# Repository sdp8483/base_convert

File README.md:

# Base Convert Rev A 
## Introduction
Base Convert PL-47710 Rev. A is a simple desk/handheld device to convert between hexadecimal, decimal, and binary. The unit features separate displays for each number base for easy comparison between the three bases. User input is possible using 16 alphanumeric keys and an input mode selector switch. The device is powered by 4 AA alkaline batteries with an estimated 100 hours of battery life.

## Specifications
|Item             |Specification               |
|:----------------|:--------------------------:|
|Hex Display      |4 digit, 7 segment red LED  |
|Decimal Display  |6 digit, 7 segment red LED  |
|Binary Display   |16 red LEDs                 |
|User Input       |16 digit alphanumeric keypad|
|Power            |4 AA Alkaline               |
|Battery Life     |100 hrs estimated           |
|Width            |94mm / 3.7"                 |
|Height           |100mm / 3.94"               |
|Thickness        |35mm / 1.38"                |
|Weight, with 4xAA|275g / 9.65oz               |

## Layout

1. Hexadecimal Display
2. Decimal Display
3. Binary Display
4. Power and Input Selection Switch
5. Alphanumeric Input Keypad
6. Programming Port (Right Angle Header on Side)

## Installing Batteries
Using a 1.5mm hex bit remove the eight M2.5 button head hex bolts holding the back panel to the unit. Install 4x AA batteries into the battery holder attached to the main PCB. Follow the polarity imprinted on the battery holder. The device does have reverse polarity projection that should project it from damage but it is still advisable to not reverse the polarity of the batteries. Replace the back panel after installing the batteries.

## Use
To turn on the unit slide the selector switch from the OFF position to any of the three input positions. The display will illuminate at the default value of 0.

### To Input Hexadecimal Number
Slide the selector switch to *HEX*. The right most decimal on the hexadecimal display will illuminate when the unit is in hexadecimal input mode. Use the alphanumeric keypad to input a hexadecimal number, all three displays will update after each key press. If the hexadecimal number exceeds 4 digits the left most digit will be dropped to shift in the right most digit. Clearing the display by pressing the *CLEAR* button will set the hexadecimal number to 0.

### To Input Decimal Number
Slide the selector switch to *DEC*. The right most decimal on the decimal display will illuminate when the unit is in decimal input mode. Use the alphanumeric keypad to input a decimal number, all three displays will update after each key press. If the decimal number will exceed 65,535 with the requested key press the device will no longer shift in new decimal digits while in decimal input mode. Clearing the display will set the decimal number to 0.

### To Input Binary Number
Slide the selector switch to *BIN*. There is no indicator on any of the displays to indicate that the unit is in binary input mode. Use the alphanumeric keypad to toggle the bits of the binary number displayed on the binary display, all three displays will update after each key press. Pressing the *CLEAR* button will set the binary number to 0.

## Updating Firmware
It is possible to update the firmware. A TI Launchpad and cable is required. The pin out of the programming header is as follows when looking at the unit from the front.

- 3.3V
- SBWTDIO
- SBWTCK
- GND

External power is required, install 4x AA batteries before updating the firmware and place the selector switch in any of the input positions.

The most current firmware is located here: https://github.com/sdp8483/base_convert/tree/master/firmware/base_convert
CCS 8.x.x or newer is required to update the firmware. Please search online for help using CCS and uploading firmware since this is outside of the scope of this document.

## Future Fixes
- [ ] Silkscreen label of programming interface connections/pins
- [ ] Silkscreen label of power connector + and - pins
- [ ] add space for solder iron around resistor networks
- [ ] battery low indicator in SW, should have HW to do it
- [ ] at 6V the display will not turn off when the PNP are pulled high (cant pull it high enough) 
  Placing a 1k resistor between the base and emitter of each PNP solves the problem but it appears 
  like there is an issue caused with the 3.3V LDO since the voltage to the uC is 4.1V or so not the 3.3V it should be.
  Going to see if 3V for the battery is bright enough and maybe switch to 2AA as battery or go to LiPo in the future.
- [ ] Swap C2 and C4 on PCB so that the correct capacitor is near the correct IC
- [ ] Easy firmware update method --LOW PRIORITY

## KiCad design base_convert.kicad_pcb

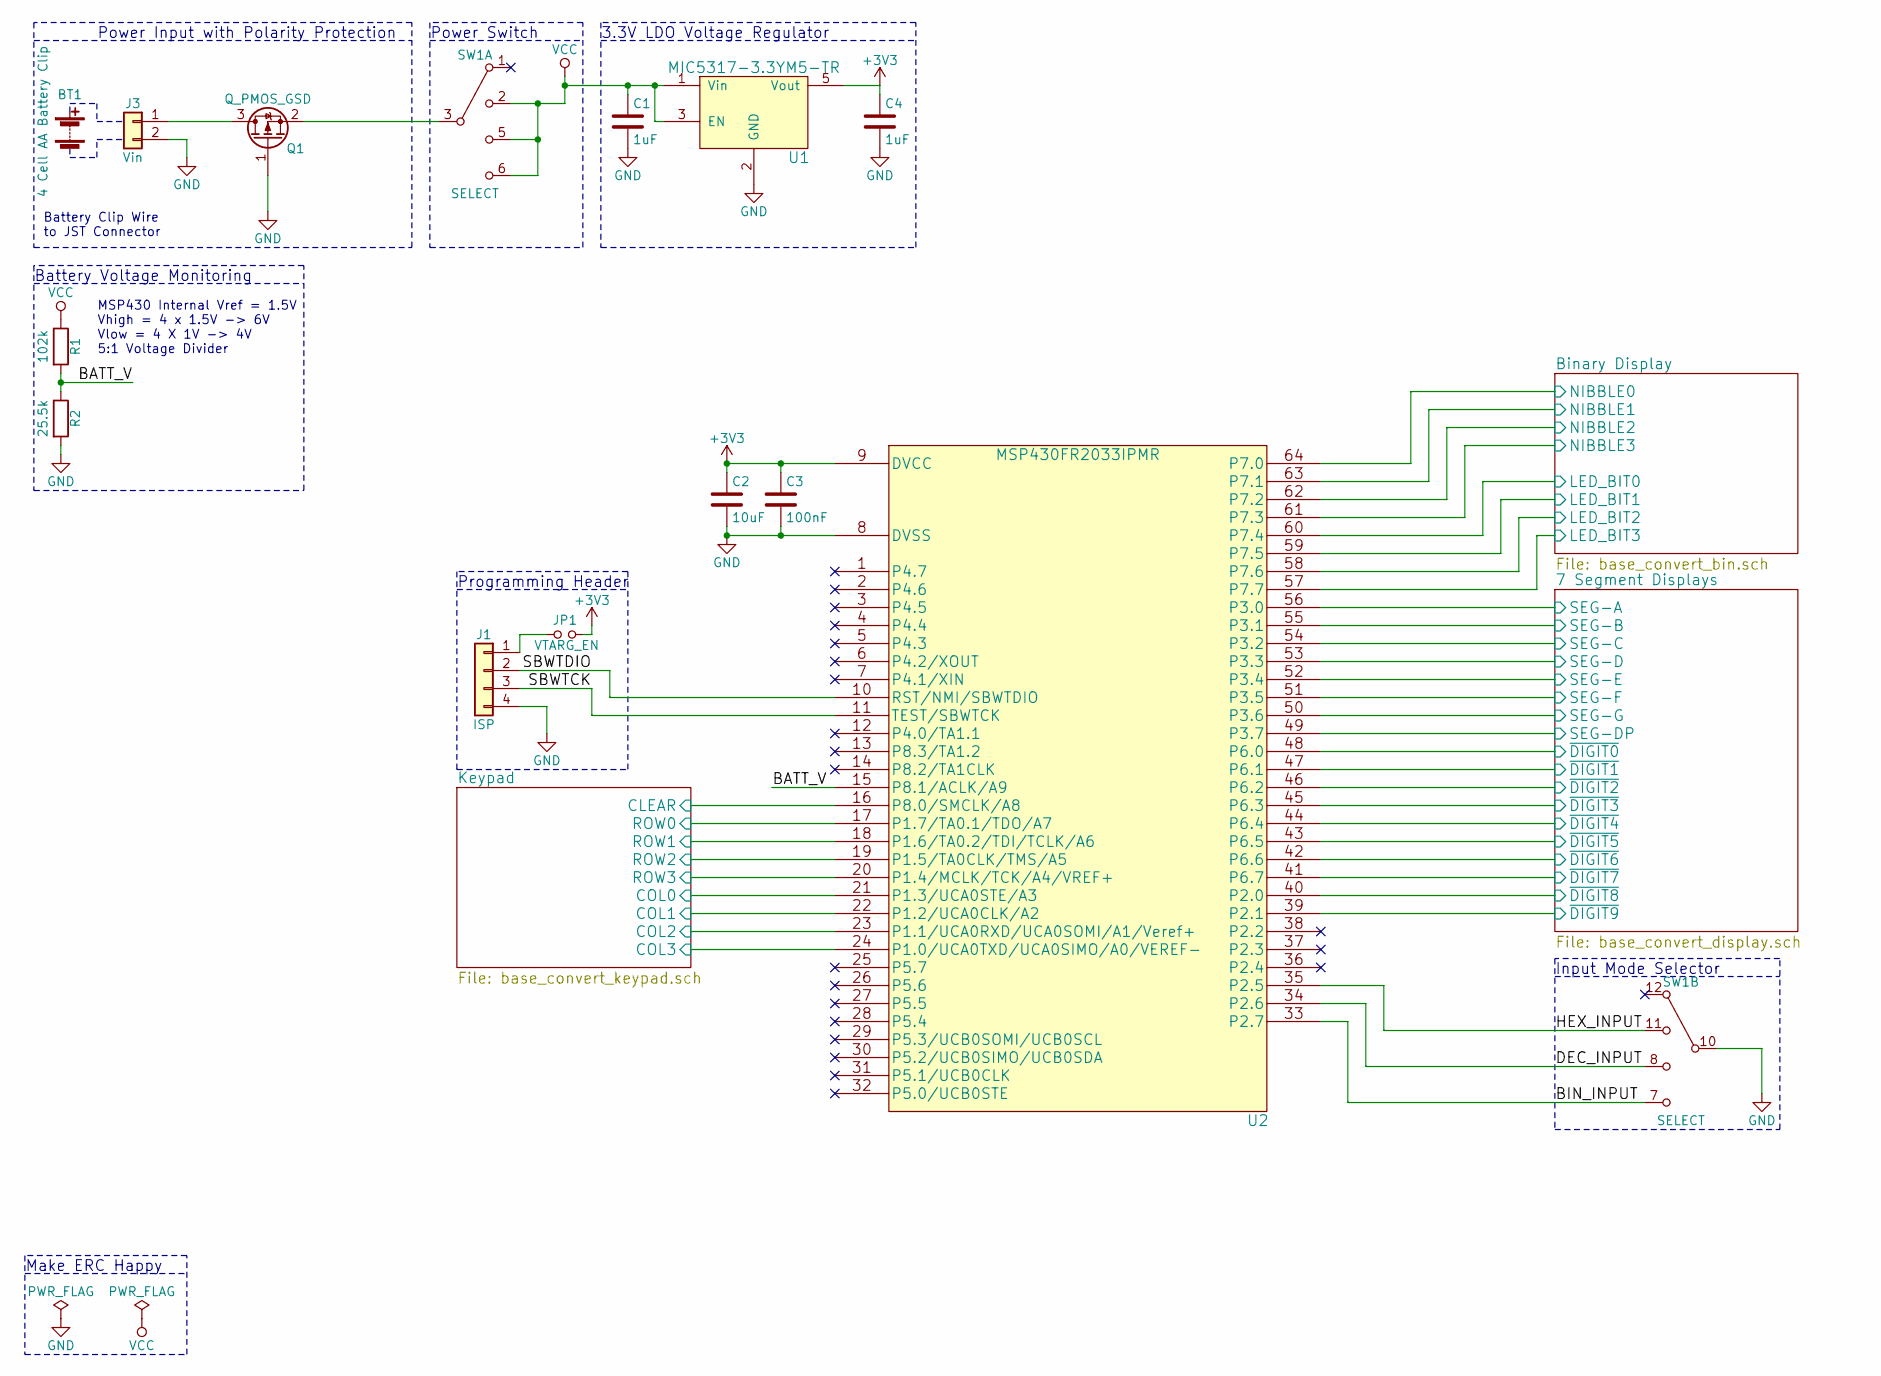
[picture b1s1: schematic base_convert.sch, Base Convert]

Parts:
BT1: 4 Cell AA Battery Clip; BC4AAW; Mfg Part Number BC4AAW
C1, C4: 1uF; C_0805; Mfg Part Number CL21B105KOFNNNG
C2: 10uF; C_0805; Mfg Part Number CL21A106KQFNNNG
C3: 100nF; C_0805; Mfg Part Number CL21B104KOANNNC
J1: ISP; Pin_Header_Straight_1x04_Pitch2.54mm
J3: Vin; JST_PH_S2B-PH-K_02x2.00mm_Angled; Mfg Part Number S2B-PH-K-S(LF)(SN)
JP1: VTARG_EN; R_1206; Mfg Part Number RC1206JR-070RL
Q1: Q_PMOS_GSD; SOT-23; Mfg Part Number SI2323DDS-T1-GE3
R1: 102k; R_0603; Mfg Part Number MCR03ERTF1023
R2: 25.5k; R_0603; Mfg Part Number MCR03ERTF2552
SW1: SELECT; DP4T_SS-24E06-TG5P; Mfg Part Number SS-24E06-TG 5 (P)
U1: MIC5317-3.3YM5-TR; SOT-23-5; Mfg Part Number MIC5317-3.3YM5-TR
U2: MSP430FR2033IPMR; LQFP-64_10x10mm_Pitch0.5mm; Mfg Part Number MSP430FR2033IPMR

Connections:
+3V3: C2.1, C3.1, C4.1, JP1.2, U1.5 (Vout), U2.9 (DVCC)
/7 Segment Displays/SEG-A: U2.56 (P3.0); also elsewhere on the board
/7 Segment Displays/SEG-B: U2.55 (P3.1); also elsewhere on the board
/7 Segment Displays/SEG-C: U2.54 (P3.2); also elsewhere on the board
/7 Segment Displays/SEG-D: U2.53 (P3.3); also elsewhere on the board
/7 Segment Displays/SEG-DP: U2.49 (P3.7); also elsewhere on the board
/7 Segment Displays/SEG-E: U2.52 (P3.4); also elsewhere on the board
/7 Segment Displays/SEG-F: U2.51 (P3.5); also elsewhere on the board
/7 Segment Displays/SEG-G: U2.50 (P3.6); also elsewhere on the board
/7 Segment Displays/~DIGIT0: U2.48 (P6.0); also elsewhere on the board
/7 Segment Displays/~DIGIT1: U2.47 (P6.1); also elsewhere on the board
/7 Segment Displays/~DIGIT2: U2.46 (P6.2); also elsewhere on the board
/7 Segment Displays/~DIGIT3: U2.45 (P6.3); also elsewhere on the board
/7 Segment Displays/~DIGIT4: U2.44 (P6.4); also elsewhere on the board
/7 Segment Displays/~DIGIT5: U2.43 (P6.5); also elsewhere on the board
/7 Segment Displays/~DIGIT6: U2.42 (P6.6); also elsewhere on the board
/7 Segment Displays/~DIGIT7: U2.41 (P6.7); also elsewhere on the board
/7 Segment Displays/~DIGIT8: U2.40 (P2.0); also elsewhere on the board
/7 Segment Displays/~DIGIT9: U2.39 (P2.1); also elsewhere on the board
/BATT_V: R1.2, R2.1, U2.15 (P8.1/ACLK/A9)
/BIN_INPUT: SW1.7 (D), U2.33 (P2.7)
/Binary Display/LED_BIT0: U2.60 (P7.4); also elsewhere on the board
/Binary Display/LED_BIT1: U2.59 (P7.5); also elsewhere on the board
/Binary Display/LED_BIT2: U2.58 (P7.6); also elsewhere on the board
/Binary Display/LED_BIT3: U2.57 (P7.7); also elsewhere on the board
/Binary Display/NIBBLE0: U2.64 (P7.0); also elsewhere on the board
/Binary Display/NIBBLE1: U2.63 (P7.1); also elsewhere on the board
/Binary Display/NIBBLE2: U2.62 (P7.2); also elsewhere on the board
/Binary Display/NIBBLE3: U2.61 (P7.3); also elsewhere on the board
/DEC_INPUT: SW1.8 (C), U2.34 (P2.6)
/HEX_INPUT: SW1.11 (B), U2.35 (P2.5)
/Keypad/CLEAR: U2.16 (P8.0/SMCLK/A8); also elsewhere on the board
/Keypad/COL0: U2.21 (P1.3/UCA0STE/A3); also elsewhere on the board
/Keypad/COL1: U2.22 (P1.2/UCA0CLK/A2); also elsewhere on the board
/Keypad/COL2: U2.23 (P1.1/UCA0RXD/UCA0SOMI/A1/Veref+); also elsewhere on the board
/Keypad/COL3: U2.24 (P1.0/UCA0TXD/UCA0SIMO/A0/VEREF-); also elsewhere on the board
/Keypad/ROW0: U2.17 (P1.7/TA0.1/TDO/A7); also elsewhere on the board
/Keypad/ROW1: U2.18 (P1.6/TA0.2/TDI/TCLK/A6); also elsewhere on the board
/Keypad/ROW2: U2.19 (P1.5/TA0CLK/TMS/A5); also elsewhere on the board
/Keypad/ROW3: U2.20 (P1.4/MCLK/TCK/A4/VREF+); also elsewhere on the board
/SBWTCK: J1.3, U2.11 (TEST/SBWTCK)
/SBWTDIO: J1.2, U2.10 (RST/NMI/SBWTDIO)
GND: C1.2, C2.2, C3.2, C4.2, J1.4, J3.2, Q1.1 (G), R2.2, SW1.10 (COM), U1.2 (GND), U2.8 (DVSS); also elsewhere on the board
unnamed: J1.1, JP1.1
unnamed: J3.1, Q1.3 (D)
unnamed: Q1.2 (S), SW1.3 (COM)
VCC: C1.1, R1.1, SW1.2 (B), SW1.5 (C), SW1.6 (D), U1.1 (Vin), U1.3 (EN); also elsewhere on the board

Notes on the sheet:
Programming Header
3.3V LDO Voltage Regulator
Input Mode Selector
Power Input with Polarity Protection
Power Switch
MSP430 Internal Vref = 1.5V Vhigh = 4 x 1.5V -> 6V Vlow = 4 X 1V -> 4V 5:1 Voltage Divider
Battery Voltage Monitoring
Battery Clip Wire to JST Connector
Make ERC Happy

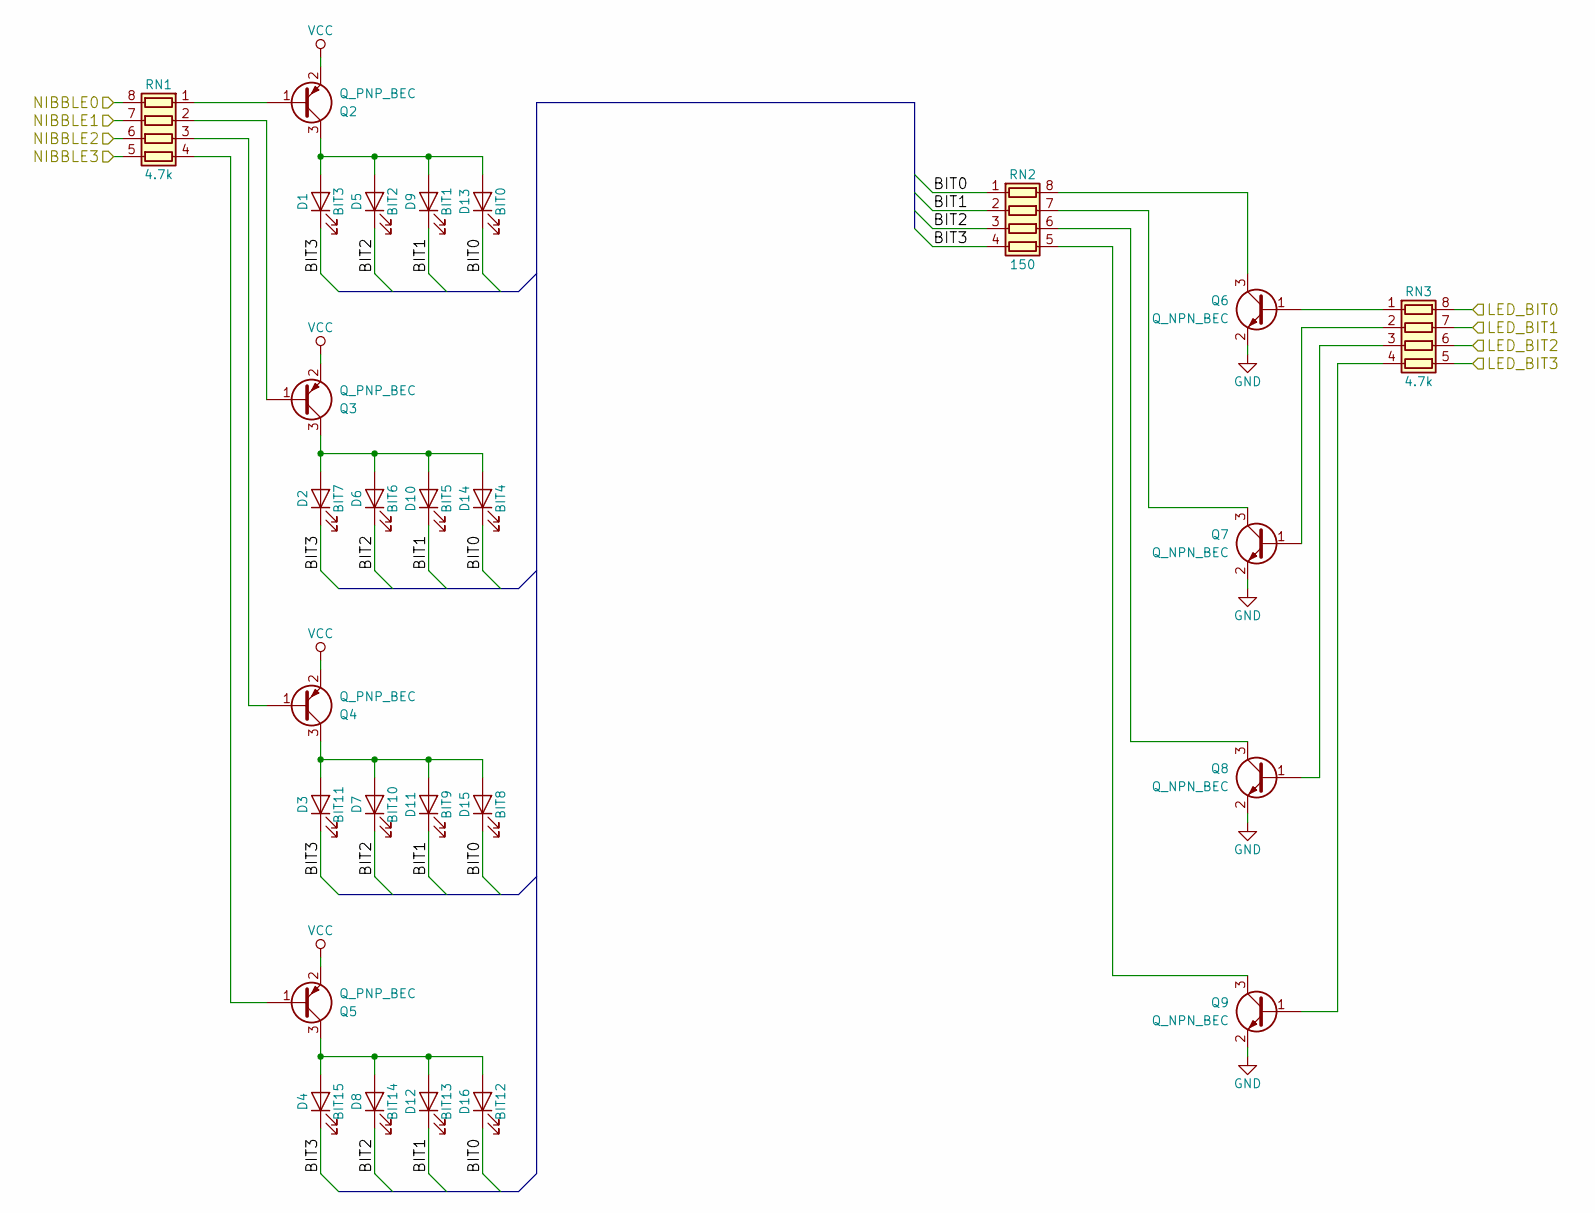
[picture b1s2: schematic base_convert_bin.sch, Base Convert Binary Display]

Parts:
D1: BIT3; LED_0805_LightPipe_VLP; Mfg Part Number 150080RS75000
D2: BIT7; LED_0805_LightPipe_VLP; Mfg Part Number 150080RS75008
D3: BIT11; LED_0805_LightPipe_VLP; Mfg Part Number 150080RS75009
D4: BIT15; LED_0805_LightPipe_VLP; Mfg Part Number 150080RS75010
D5: BIT2; LED_0805_LightPipe_VLP; Mfg Part Number 150080RS75011
D6: BIT6; LED_0805_LightPipe_VLP; Mfg Part Number 150080RS75012
D7: BIT10; LED_0805_LightPipe_VLP; Mfg Part Number 150080RS75013
D8: BIT14; LED_0805_LightPipe_VLP; Mfg Part Number 150080RS75014
D9: BIT1; LED_0805_LightPipe_VLP; Mfg Part Number 150080RS75015
D10: BIT5; LED_0805_LightPipe_VLP; Mfg Part Number 150080RS75001
D11: BIT9; LED_0805_LightPipe_VLP; Mfg Part Number 150080RS75002
D12: BIT13; LED_0805_LightPipe_VLP; Mfg Part Number 150080RS75003
D13: BIT0; LED_0805_LightPipe_VLP; Mfg Part Number 150080RS75004
D14: BIT4; LED_0805_LightPipe_VLP; Mfg Part Number 150080RS75005
D15: BIT8; LED_0805_LightPipe_VLP; Mfg Part Number 150080RS75006
D16: BIT12; LED_0805_LightPipe_VLP; Mfg Part Number 150080RS75007
Q2: Q_PNP_BEC; SOT-23; Mfg Part Number PMBT3906,235
Q3: Q_PNP_BEC; SOT-23; Mfg Part Number PMBT3906,236
Q4: Q_PNP_BEC; SOT-23; Mfg Part Number PMBT3906,238
Q5: Q_PNP_BEC; SOT-23; Mfg Part Number PMBT3906,239
Q6, Q7, Q8, Q9: Q_NPN_BEC; SOT-23; Mfg Part Number MMBT3904L RFG
RN1, RN3: 4.7k; R_Array_Convex_4x1206; Mfg Part Number RAVF164DJT4K70
RN2: 150; R_Array_Convex_4x1206; Mfg Part Number MNR14ERAPJ151

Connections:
/Binary Display/BIT0: D13.1 (K), D14.1 (K), D15.1 (K), D16.1 (K), RN2.1 (R1.1)
/Binary Display/BIT1: D9.1 (K), D10.1 (K), D11.1 (K), D12.1 (K), RN2.2 (R2.1)
/Binary Display/BIT2: D5.1 (K), D6.1 (K), D7.1 (K), D8.1 (K), RN2.3 (R3.1)
/Binary Display/BIT3: D1.1 (K), D2.1 (K), D3.1 (K), D4.1 (K), RN2.4 (R4.1)
/Binary Display/LED_BIT0: RN3.8 (R1.2); also elsewhere on the board
/Binary Display/LED_BIT1: RN3.7 (R2.2); also elsewhere on the board
/Binary Display/LED_BIT2: RN3.6 (R3.2); also elsewhere on the board
/Binary Display/LED_BIT3: RN3.5 (R4.2); also elsewhere on the board
/Binary Display/NIBBLE0: RN1.8 (R1.2); also elsewhere on the board
/Binary Display/NIBBLE1: RN1.7 (R2.2); also elsewhere on the board
/Binary Display/NIBBLE2: RN1.6 (R3.2); also elsewhere on the board
/Binary Display/NIBBLE3: RN1.5 (R4.2); also elsewhere on the board
GND: Q6.2 (E), Q7.2 (E), Q8.2 (E), Q9.2 (E); also elsewhere on the board
unnamed: D1.2 (A), D5.2 (A), D9.2 (A), D13.2 (A), Q2.3 (C)
unnamed: D2.2 (A), D6.2 (A), D10.2 (A), D14.2 (A), Q3.3 (C)
unnamed: D3.2 (A), D7.2 (A), D11.2 (A), D15.2 (A), Q4.3 (C)
unnamed: D4.2 (A), D8.2 (A), D12.2 (A), D16.2 (A), Q5.3 (C)
unnamed: Q2.1 (B), RN1.1 (R1.1)
unnamed: Q3.1 (B), RN1.2 (R2.1)
unnamed: Q4.1 (B), RN1.3 (R3.1)
unnamed: Q5.1 (B), RN1.4 (R4.1)
unnamed: Q6.1 (B), RN3.1 (R1.1)
unnamed: Q6.3 (C), RN2.8 (R1.2)
unnamed: Q7.1 (B), RN3.2 (R2.1)
unnamed: Q7.3 (C), RN2.7 (R2.2)
unnamed: Q8.1 (B), RN3.3 (R3.1)
unnamed: Q8.3 (C), RN2.6 (R3.2)
unnamed: Q9.1 (B), RN3.4 (R4.1)
unnamed: Q9.3 (C), RN2.5 (R4.2)
VCC: Q2.2 (E), Q3.2 (E), Q4.2 (E), Q5.2 (E); also elsewhere on the board

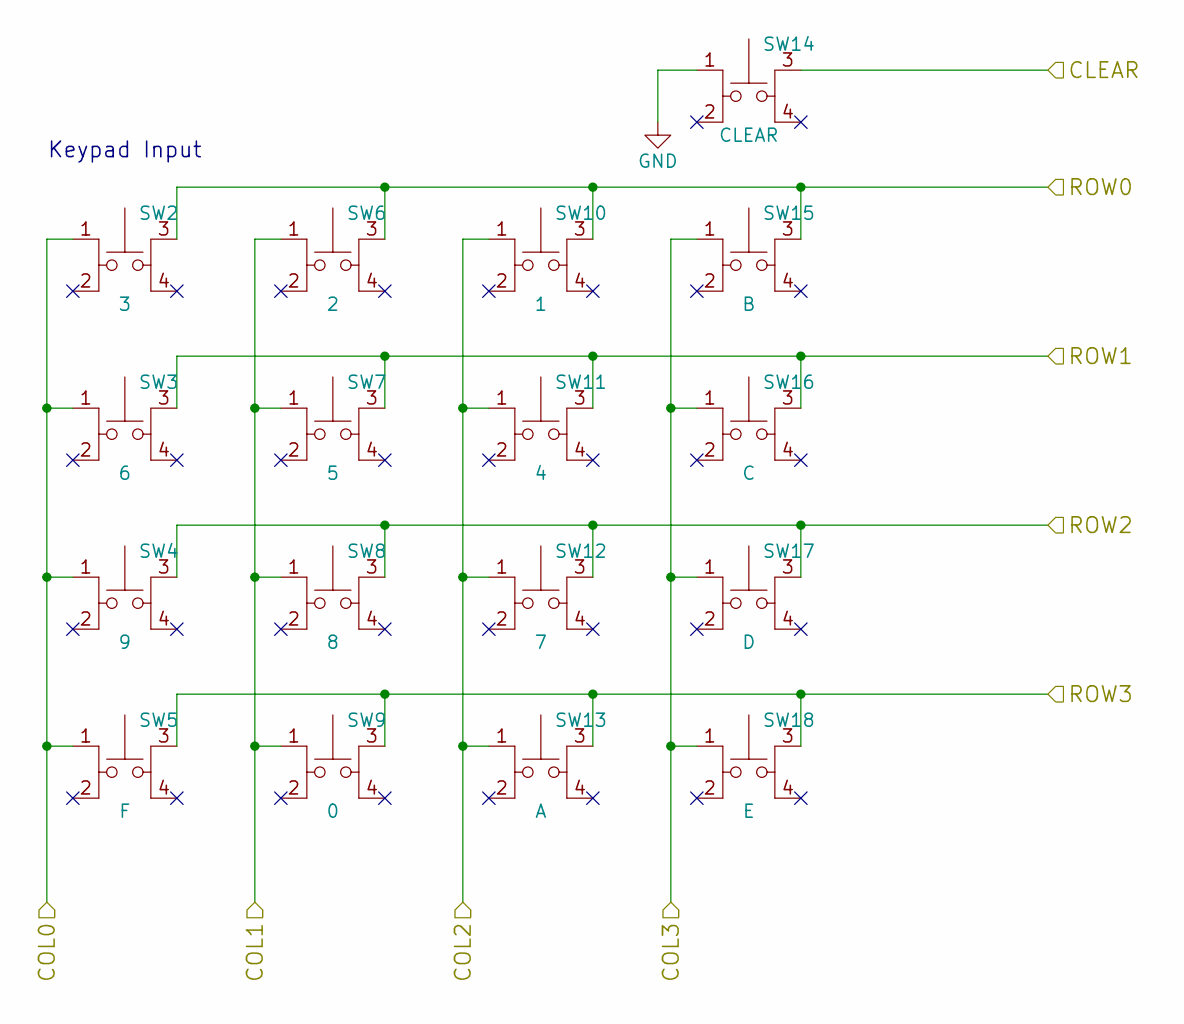
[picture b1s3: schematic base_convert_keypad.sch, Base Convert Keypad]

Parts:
SW2: 3; CK_PTS645_6mm_SMD; Mfg Part Number PTS645SK13SMTR92LFS
SW3: 6; CK_PTS645_6mm_SMD; Mfg Part Number PTS645SK13SMTR92LFS
SW4: 9; CK_PTS645_6mm_SMD; Mfg Part Number PTS645SK13SMTR92LFS
SW5: F; CK_PTS645_6mm_SMD; Mfg Part Number PTS645SK13SMTR92LFS
SW6: 2; CK_PTS645_6mm_SMD; Mfg Part Number PTS645SK13SMTR92LFS
SW7: 5; CK_PTS645_6mm_SMD; Mfg Part Number PTS645SK13SMTR92LFS
SW8: 8; CK_PTS645_6mm_SMD; Mfg Part Number PTS645SK13SMTR92LFS
SW9: 0; CK_PTS645_6mm_SMD; Mfg Part Number PTS645SK13SMTR92LFS
SW10: 1; CK_PTS645_6mm_SMD; Mfg Part Number PTS645SK13SMTR92LFS
SW11: 4; CK_PTS645_6mm_SMD; Mfg Part Number PTS645SK13SMTR92LFS
SW12: 7; CK_PTS645_6mm_SMD; Mfg Part Number PTS645SK13SMTR92LFS
SW13: A; CK_PTS645_6mm_SMD; Mfg Part Number PTS645SK13SMTR92LFS
SW14: CLEAR; CK_PTS645_6mm_SMD; Mfg Part Number PTS645SK13SMTR92LFS
SW15: B; CK_PTS645_6mm_SMD; Mfg Part Number PTS645SK13SMTR92LFS
SW16: C; CK_PTS645_6mm_SMD; Mfg Part Number PTS645SK13SMTR92LFS
SW17: D; CK_PTS645_6mm_SMD; Mfg Part Number PTS645SK13SMTR92LFS
SW18: E; CK_PTS645_6mm_SMD; Mfg Part Number PTS645SK13SMTR92LFS

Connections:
/Keypad/CLEAR: SW14.3; also elsewhere on the board
/Keypad/COL0: SW2.1, SW3.1, SW4.1, SW5.1; also elsewhere on the board
/Keypad/COL1: SW6.1, SW7.1, SW8.1, SW9.1; also elsewhere on the board
/Keypad/COL2: SW10.1, SW11.1, SW12.1, SW13.1; also elsewhere on the board
/Keypad/COL3: SW15.1, SW16.1, SW17.1, SW18.1; also elsewhere on the board
/Keypad/ROW0: SW2.3, SW6.3, SW10.3, SW15.3; also elsewhere on the board
/Keypad/ROW1: SW3.3, SW7.3, SW11.3, SW16.3; also elsewhere on the board
/Keypad/ROW2: SW4.3, SW8.3, SW12.3, SW17.3; also elsewhere on the board
/Keypad/ROW3: SW5.3, SW9.3, SW13.3, SW18.3; also elsewhere on the board
GND: SW14.1; also elsewhere on the board

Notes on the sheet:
Keypad Input

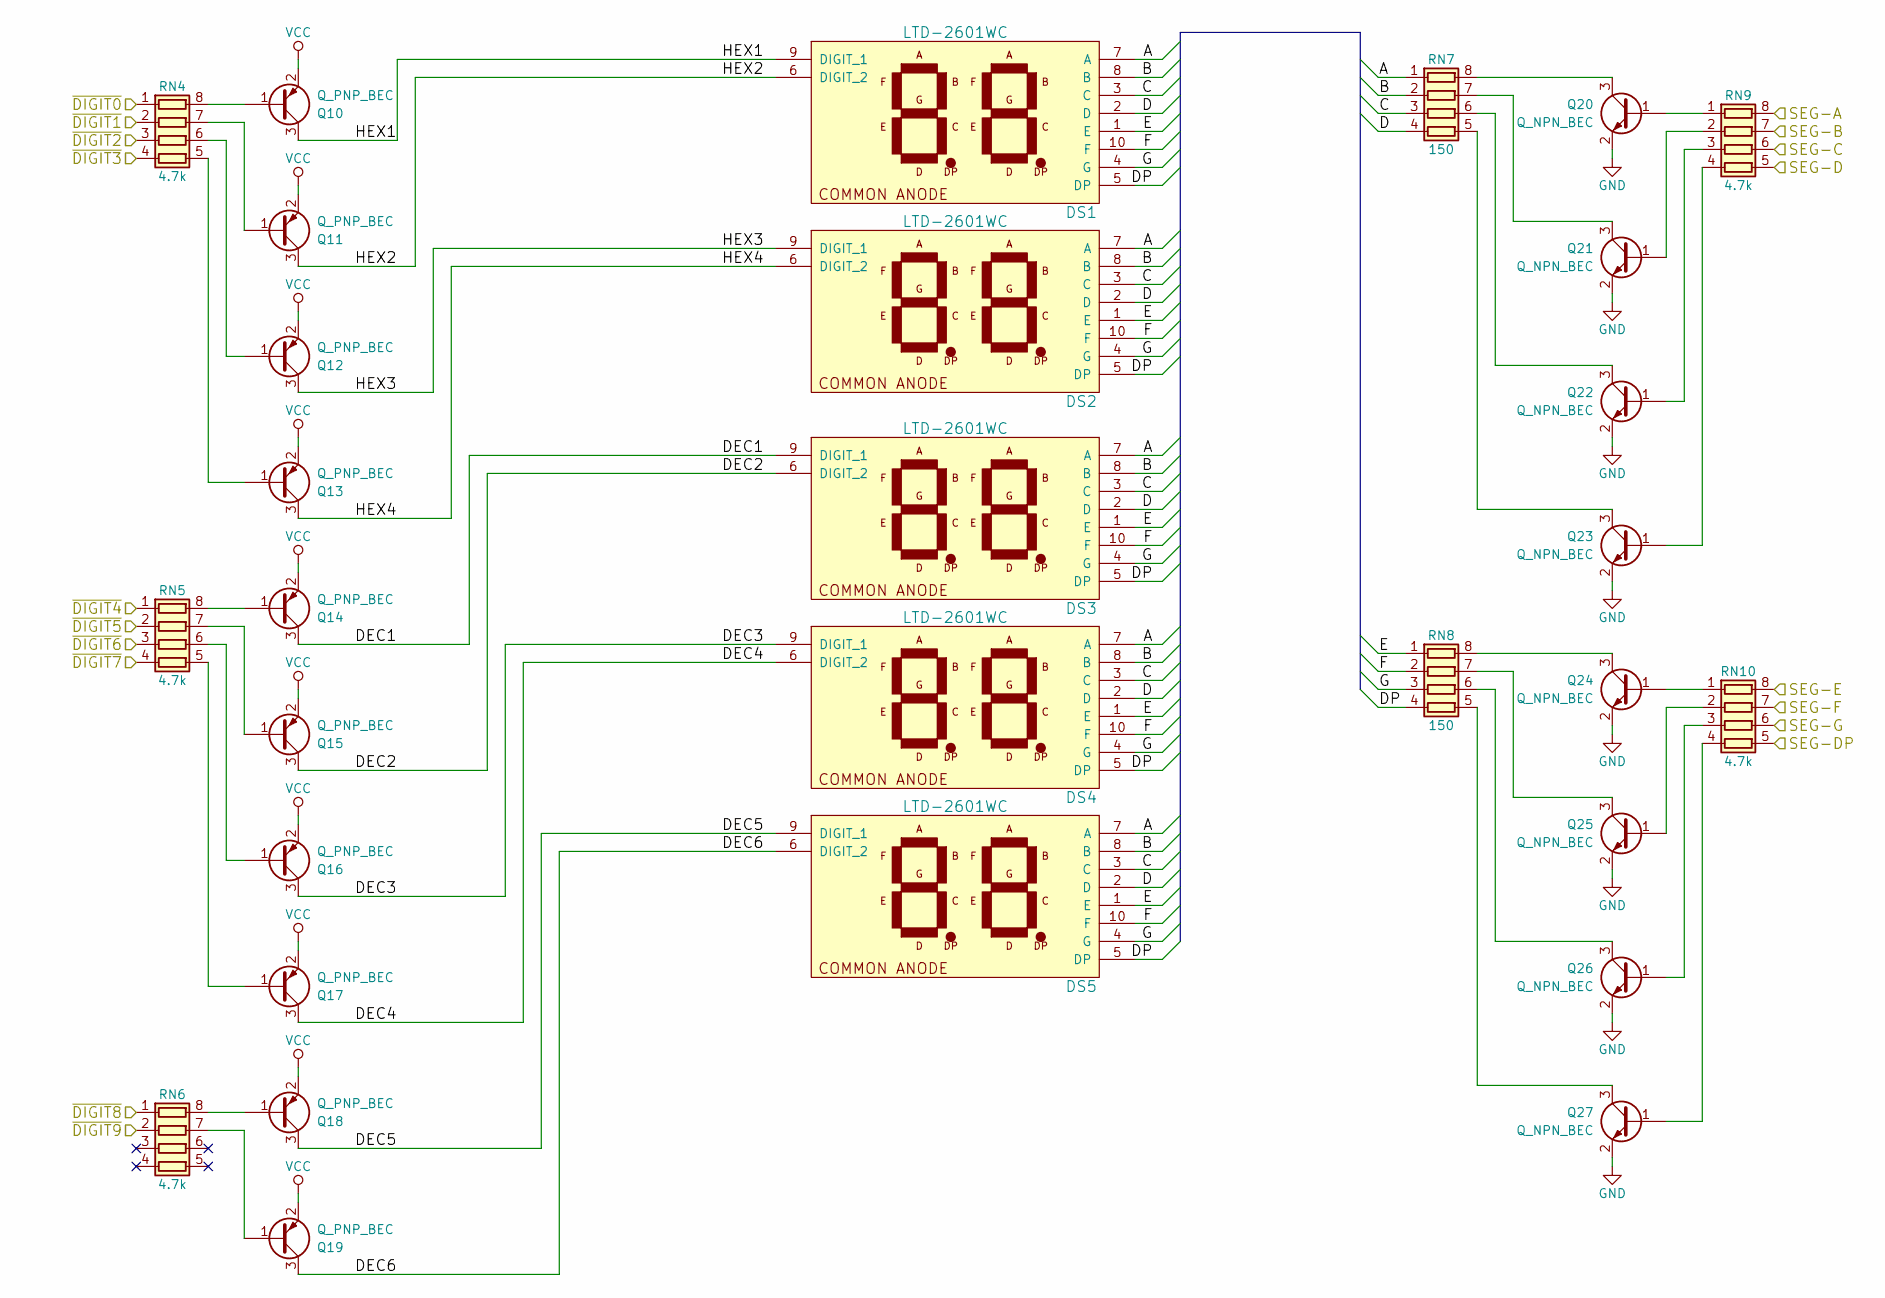
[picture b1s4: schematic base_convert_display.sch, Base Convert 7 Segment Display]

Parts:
DS1, DS2, DS3, DS4, DS5: LTD-2601WC; Display_Lite-On_LTD-2601WC; Mfg Part Number LTD-2601WC
Q10, Q13: Q_PNP_BEC; SOT-23; Mfg Part Number PMBT3906,237
Q11, Q18, Q19: Q_PNP_BEC; SOT-23; Mfg Part Number PMBT3906,235
Q12: Q_PNP_BEC; SOT-23; Mfg Part Number PMBT3906,236
Q14: Q_PNP_BEC; SOT-23; Mfg Part Number PMBT3906,238
Q15: Q_PNP_BEC; SOT-23; Mfg Part Number PMBT3906,239
Q16: Q_PNP_BEC; SOT-23; Mfg Part Number PMBT3906,240
Q17: Q_PNP_BEC; SOT-23; Mfg Part Number PMBT3906,241
Q20, Q21, Q22, Q23, Q24, Q25, Q26, Q27: Q_NPN_BEC; SOT-23; Mfg Part Number MMBT3904L RFG
RN4, RN5, RN6, RN9, RN10: 4.7k; R_Array_Convex_4x1206; Mfg Part Number RAVF164DJT4K70
RN7, RN8: 150; R_Array_Convex_4x1206; Mfg Part Number MNR14ERAPJ151

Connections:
/7 Segment Displays/A: DS1.7 (A), DS2.7 (A), DS3.7 (A), DS4.7 (A), DS5.7 (A), RN7.1 (R1.1)
/7 Segment Displays/B: DS1.8 (B), DS2.8 (B), DS3.8 (B), DS4.8 (B), DS5.8 (B), RN7.2 (R2.1)
/7 Segment Displays/C: DS1.3 (C), DS2.3 (C), DS3.3 (C), DS4.3 (C), DS5.3 (C), RN7.3 (R3.1)
/7 Segment Displays/D: DS1.2 (D), DS2.2 (D), DS3.2 (D), DS4.2 (D), DS5.2 (D), RN7.4 (R4.1)
/7 Segment Displays/DEC1: DS3.9 (DIGIT_1), Q14.3 (C)
/7 Segment Displays/DEC2: DS3.6 (DIGIT_2), Q15.3 (C)
/7 Segment Displays/DEC3: DS4.9 (DIGIT_1), Q16.3 (C)
/7 Segment Displays/DEC4: DS4.6 (DIGIT_2), Q17.3 (C)
/7 Segment Displays/DEC5: DS5.9 (DIGIT_1), Q18.3 (C)
/7 Segment Displays/DEC6: DS5.6 (DIGIT_2), Q19.3 (C)
/7 Segment Displays/DP: DS1.5 (DP), DS2.5 (DP), DS3.5 (DP), DS4.5 (DP), DS5.5 (DP), RN8.4 (R4.1)
/7 Segment Displays/E: DS1.1 (E), DS2.1 (E), DS3.1 (E), DS4.1 (E), DS5.1 (E), RN8.1 (R1.1)
/7 Segment Displays/F: DS1.10 (F), DS2.10 (F), DS3.10 (F), DS4.10 (F), DS5.10 (F), RN8.2 (R2.1)
/7 Segment Displays/G: DS1.4 (G), DS2.4 (G), DS3.4 (G), DS4.4 (G), DS5.4 (G), RN8.3 (R3.1)
/7 Segment Displays/HEX1: DS1.9 (DIGIT_1), Q10.3 (C)
/7 Segment Displays/HEX2: DS1.6 (DIGIT_2), Q11.3 (C)
/7 Segment Displays/HEX3: DS2.9 (DIGIT_1), Q12.3 (C)
/7 Segment Displays/HEX4: DS2.6 (DIGIT_2), Q13.3 (C)
/7 Segment Displays/SEG-A: RN9.8 (R1.2); also elsewhere on the board
/7 Segment Displays/SEG-B: RN9.7 (R2.2); also elsewhere on the board
/7 Segment Displays/SEG-C: RN9.6 (R3.2); also elsewhere on the board
/7 Segment Displays/SEG-D: RN9.5 (R4.2); also elsewhere on the board
/7 Segment Displays/SEG-DP: RN10.5 (R4.2); also elsewhere on the board
/7 Segment Displays/SEG-E: RN10.8 (R1.2); also elsewhere on the board
/7 Segment Displays/SEG-F: RN10.7 (R2.2); also elsewhere on the board
/7 Segment Displays/SEG-G: RN10.6 (R3.2); also elsewhere on the board
/7 Segment Displays/~DIGIT0: RN4.1 (R1.1); also elsewhere on the board
/7 Segment Displays/~DIGIT1: RN4.2 (R2.1); also elsewhere on the board
/7 Segment Displays/~DIGIT2: RN4.3 (R3.1); also elsewhere on the board
/7 Segment Displays/~DIGIT3: RN4.4 (R4.1); also elsewhere on the board
/7 Segment Displays/~DIGIT4: RN5.1 (R1.1); also elsewhere on the board
/7 Segment Displays/~DIGIT5: RN5.2 (R2.1); also elsewhere on the board
/7 Segment Displays/~DIGIT6: RN5.3 (R3.1); also elsewhere on the board
/7 Segment Displays/~DIGIT7: RN5.4 (R4.1); also elsewhere on the board
/7 Segment Displays/~DIGIT8: RN6.1 (R1.1); also elsewhere on the board
/7 Segment Displays/~DIGIT9: RN6.2 (R2.1); also elsewhere on the board
GND: Q20.2 (E), Q21.2 (E), Q22.2 (E), Q23.2 (E), Q24.2 (E), Q25.2 (E), Q26.2 (E), Q27.2 (E); also elsewhere on the board
unnamed: Q10.1 (B), RN4.8 (R1.2)
unnamed: Q11.1 (B), RN4.7 (R2.2)
unnamed: Q12.1 (B), RN4.6 (R3.2)
unnamed: Q13.1 (B), RN4.5 (R4.2)
unnamed: Q14.1 (B), RN5.8 (R1.2)
unnamed: Q15.1 (B), RN5.7 (R2.2)
unnamed: Q16.1 (B), RN5.6 (R3.2)
unnamed: Q17.1 (B), RN5.5 (R4.2)
unnamed: Q18.1 (B), RN6.8 (R1.2)
unnamed: Q19.1 (B), RN6.7 (R2.2)
unnamed: Q20.1 (B), RN9.1 (R1.1)
unnamed: Q20.3 (C), RN7.8 (R1.2)
unnamed: Q21.1 (B), RN9.2 (R2.1)
unnamed: Q21.3 (C), RN7.7 (R2.2)
unnamed: Q22.1 (B), RN9.3 (R3.1)
unnamed: Q22.3 (C), RN7.6 (R3.2)
unnamed: Q23.1 (B), RN9.4 (R4.1)
unnamed: Q23.3 (C), RN7.5 (R4.2)
unnamed: Q24.1 (B), RN10.1 (R1.1)
unnamed: Q24.3 (C), RN8.8 (R1.2)
unnamed: Q25.1 (B), RN10.2 (R2.1)
unnamed: Q25.3 (C), RN8.7 (R2.2)
unnamed: Q26.1 (B), RN10.3 (R3.1)
unnamed: Q26.3 (C), RN8.6 (R3.2)
unnamed: Q27.1 (B), RN10.4 (R4.1)
unnamed: Q27.3 (C), RN8.5 (R4.2)
VCC: Q10.2 (E), Q11.2 (E), Q12.2 (E), Q13.2 (E), Q14.2 (E), Q15.2 (E), Q16.2 (E), Q17.2 (E), Q18.2 (E), Q19.2 (E); also elsewhere on the board

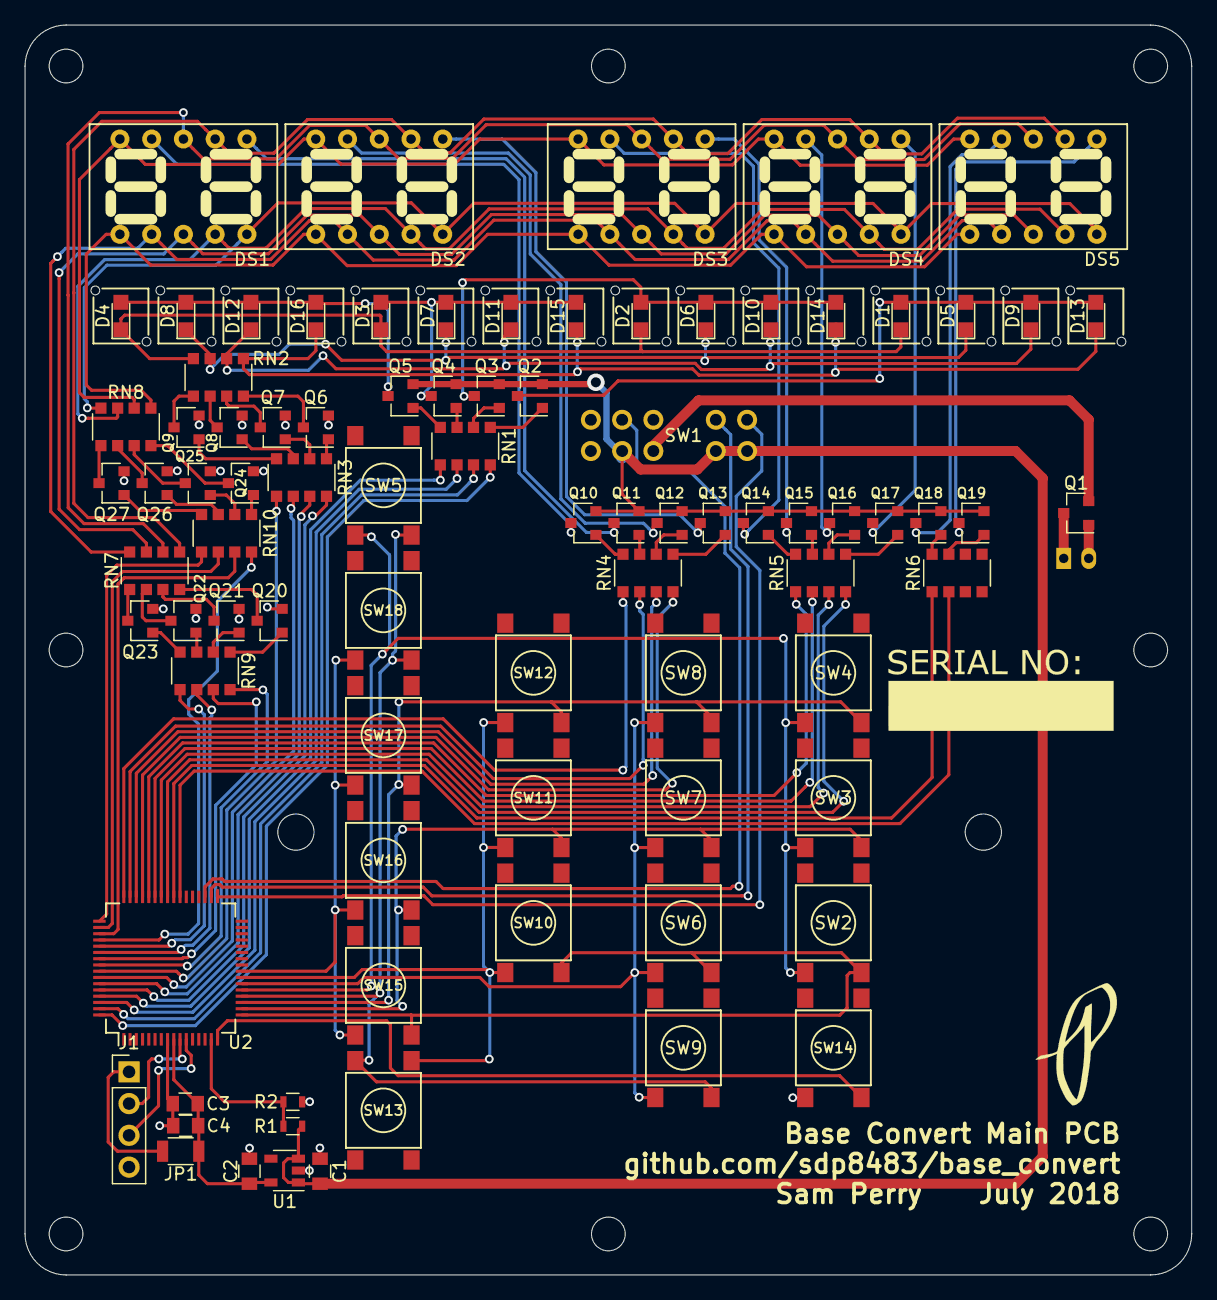
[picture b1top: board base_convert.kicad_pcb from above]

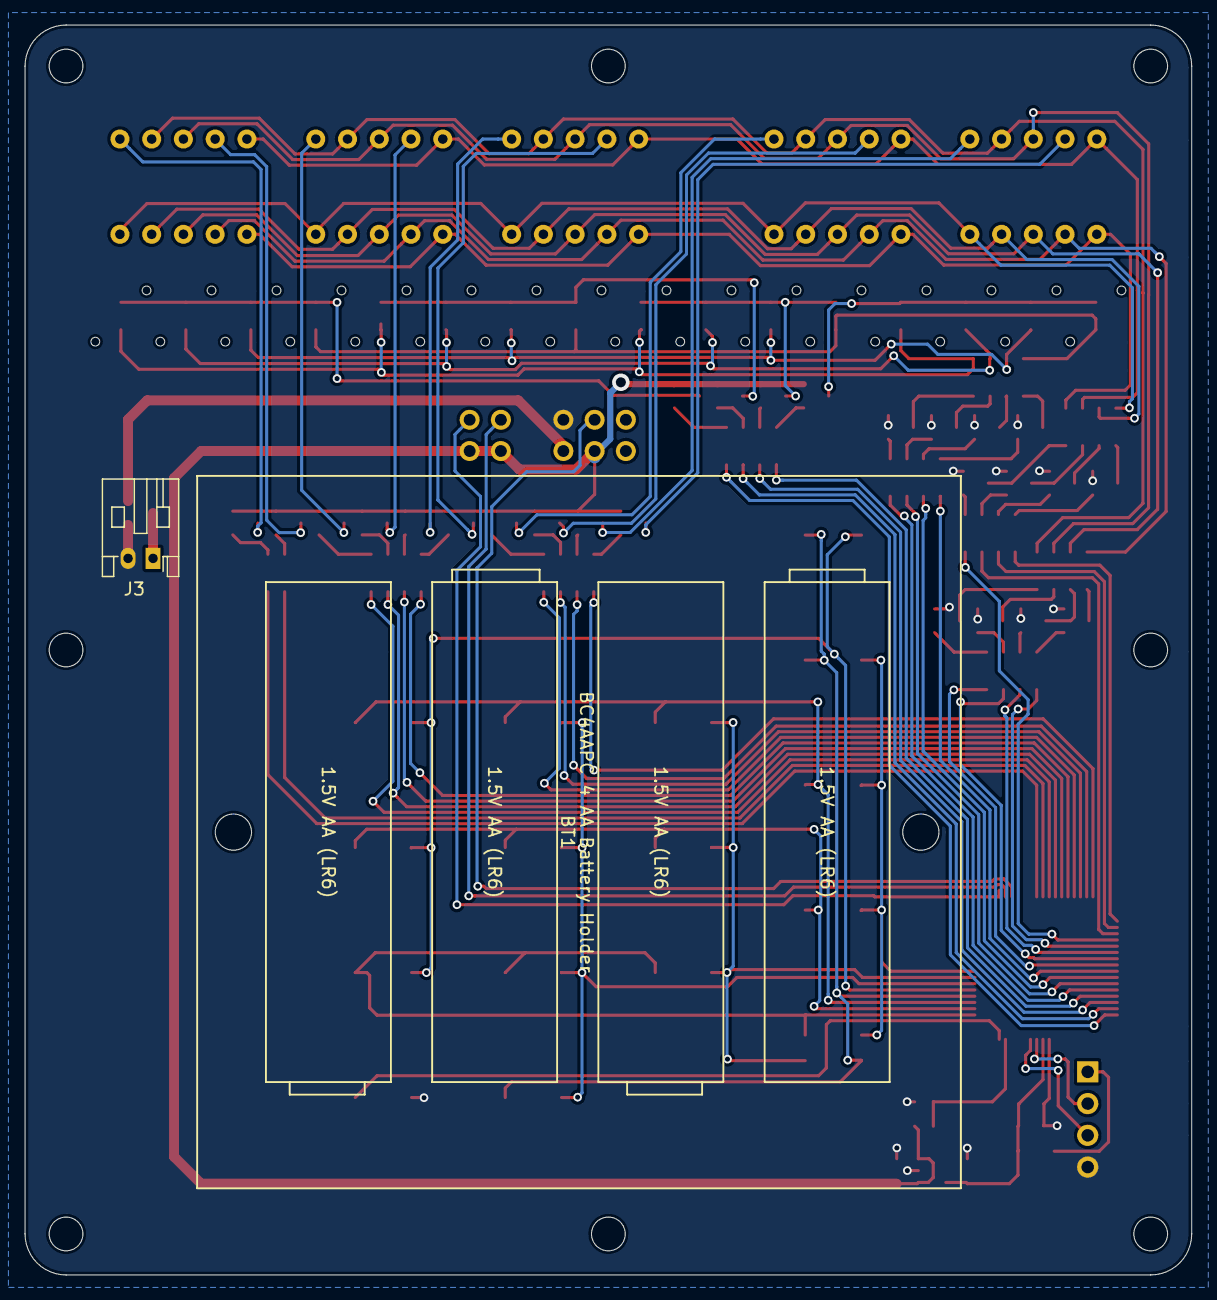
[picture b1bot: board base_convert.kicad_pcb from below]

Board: 2 copper layers, 93.3 x 100.0 mm, 88 parts (2 on the bottom side), 111 nets.

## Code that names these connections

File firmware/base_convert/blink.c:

//***************************************************************************************
//  Dirty quick 7-segment code
//
//                MSP430x5xx
//             -----------------
//         /|\|              XIN|-
//          | |                 |
//          --|RST          XOUT|-
//            |                 |
//            |             P1.0|-->LED
//
//***************************************************************************************


#include <msp430.h>
#include <stdint.h>

// Digit pin defines, port 5
#define DIGIT1 BIT0
#define DIGIT2 BIT1
#define DIGIT3 BIT2
#define DIGIT4 BIT3

#define SEG_A BIT0
#define SEG_B BIT1
#define SEG_C BIT2
#define SEG_D BIT3
#define SEG_E BIT4
#define SEG_F BIT5
#define SEG_G BIT6

#define ZERO    SEG_A | SEG_B | SEG_C | SEG_D | SEG_E | SEG_F
#define ONE     SEG_B | SEG_C
#define TWO     SEG_A | SEG_B | SEG_G | SEG_E | SEG_D
#define THREE   SEG_A | SEG_B | SEG_C | SEG_D | SEG_G
#define FOUR    SEG_B | SEG_C | SEG_G | SEG_F
#define FIVE    SEG_A | SEG_F | SEG_G | SEG_C | SEG_D
#define SIX     SEG_A | SEG_F | SEG_G | SEG_C | SEG_D | SEG_E
#define SEVEN   SEG_A | SEG_B | SEG_C
#define EIGHT   SEG_A | SEG_B | SEG_C | SEG_D | SEG_E | SEG_F | SEG_G
#define NINE    SEG_A | SEG_B | SEG_C | SEG_D | SEG_F | SEG_G
#define HEX_A   SEG_A | SEG_B | SEG_C | SEG_E | SEG_F | SEG_G
#define HEX_B   SEG_C | SEG_D | SEG_E | SEG_F | SEG_G
#define HEX_C   SEG_A | SEG_D | SEG_E | SEG_F
#define HEX_D   SEG_B | SEG_C | SEG_D | SEG_E | SEG_G
#define HEX_E   SEG_A | SEG_D | SEG_E | SEG_F | SEG_G
#define HEX_F   SEG_A | SEG_E | SEG_F | SEG_G


uint8_t count[] = {ZERO, ONE, TWO, THREE, FOUR, FIVE, SIX, SEVEN, EIGHT, NINE, HEX_A, HEX_B, HEX_C, HEX_D, HEX_E, HEX_F};

void main(void) {
    WDTCTL = WDTPW | WDTHOLD;               // Stop watchdog timer

    // Setup digit pins
    P5DIR |= DIGIT1;
    P5DIR |= DIGIT2;
    P5DIR |= DIGIT3;
    P5DIR |= DIGIT4;

    P5OUT &= ~(DIGIT1 | DIGIT2 | DIGIT3 |DIGIT4);   // make sure the digits are off to being with

    // setup segment pins
    P3DIR |= SEG_A;
    P3DIR |= SEG_B;
    P3DIR |= SEG_C;
    P3DIR |= SEG_D;
    P3DIR |= SEG_E;
    P3DIR |= SEG_F;
    P3DIR |= SEG_G;

    P3OUT |= SEG_A | SEG_B | SEG_C | SEG_D | SEG_E | SEG_F | SEG_G; // pull all high, they are off


    PM5CTL0 &= ~LOCKLPM5;                   // Disable the GPIO power-on default high-impedance mode
                                            // to activate previously configured port settings

    P5OUT |= DIGIT4;

    for(;;) {
        volatile uint8_t i = 0;
        for(i; i < sizeof(count); i++){
            P3OUT ^= count[i];
            __delay_cycles(500000);
            P3OUT ^= count[i];
        }
    }
}
